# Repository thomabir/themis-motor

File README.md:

# Themis Telescope Mount

Hardware and software for a direct-drive brushless DC motor and encoder for a telescope mount

## Control Scheme

- PWM
  - 50 to 100 kHz
  - Input: desired PWM duty cycle
  - Output: PWM signals to gate drivers
- Inner Loop: Current Control (FOC)
  - Controls flux and torque currents.
  - Runs at 10–20 kHz.
  - Inputs: Torque target (from position control loop), Phase current measurements (from current sensor), rotor electrical angle (from encoder).
  - Outputs: PWM duty cycles via inverse Park/Clarke
- Outer Loop: Position Control
  - Controls angular position and/or velocity, which is commanded from the observatory
  - Runs at 100–500 Hz.
  - Inputs: Position setpoint, measured position from encoder
  - Output: Torque command

## Motor Specifications

- Type: BLDC, direct drive (salvaged from a hoverboard)
- Quantity: 2 motors
- Electrical: 3 Phases, 30 Poles, 27 Slots, 36 V, 13 A RMS peak, 7A RMS continuous, 0.45 Ω, Y
- Mechanical: ≈ 10 Nm continuous, ≈ 1.43 Nm/A, ≈ 16 rpm/V, 350 W (estimates, not necessarily accurate)

## Encoder

DIY inductosyn, 0.05 arcseconds resolution, 1000 Hz sampling rate, custom SPI-like interface with absolute position, latency 1 ms.

## System Requirements

- Telescope Alt/Az axis control
- Tracking speed: 1 rev / 24 hr
- Slewing speed: 1 rev / 10 s
- Tracking error: < 1 arcsecond RMS
- Power: Mains
- System inertia: Low (balanced 8" SCT)

Thermal: motor will be at low currents most of the time, so convection will probably be fine, with short peaks when slewing. (Motors are from a hoverboard, which was also only passively cooled)

Mechanical: Very low backlash; bearing friction (esp. static) likely to influence control scheme.

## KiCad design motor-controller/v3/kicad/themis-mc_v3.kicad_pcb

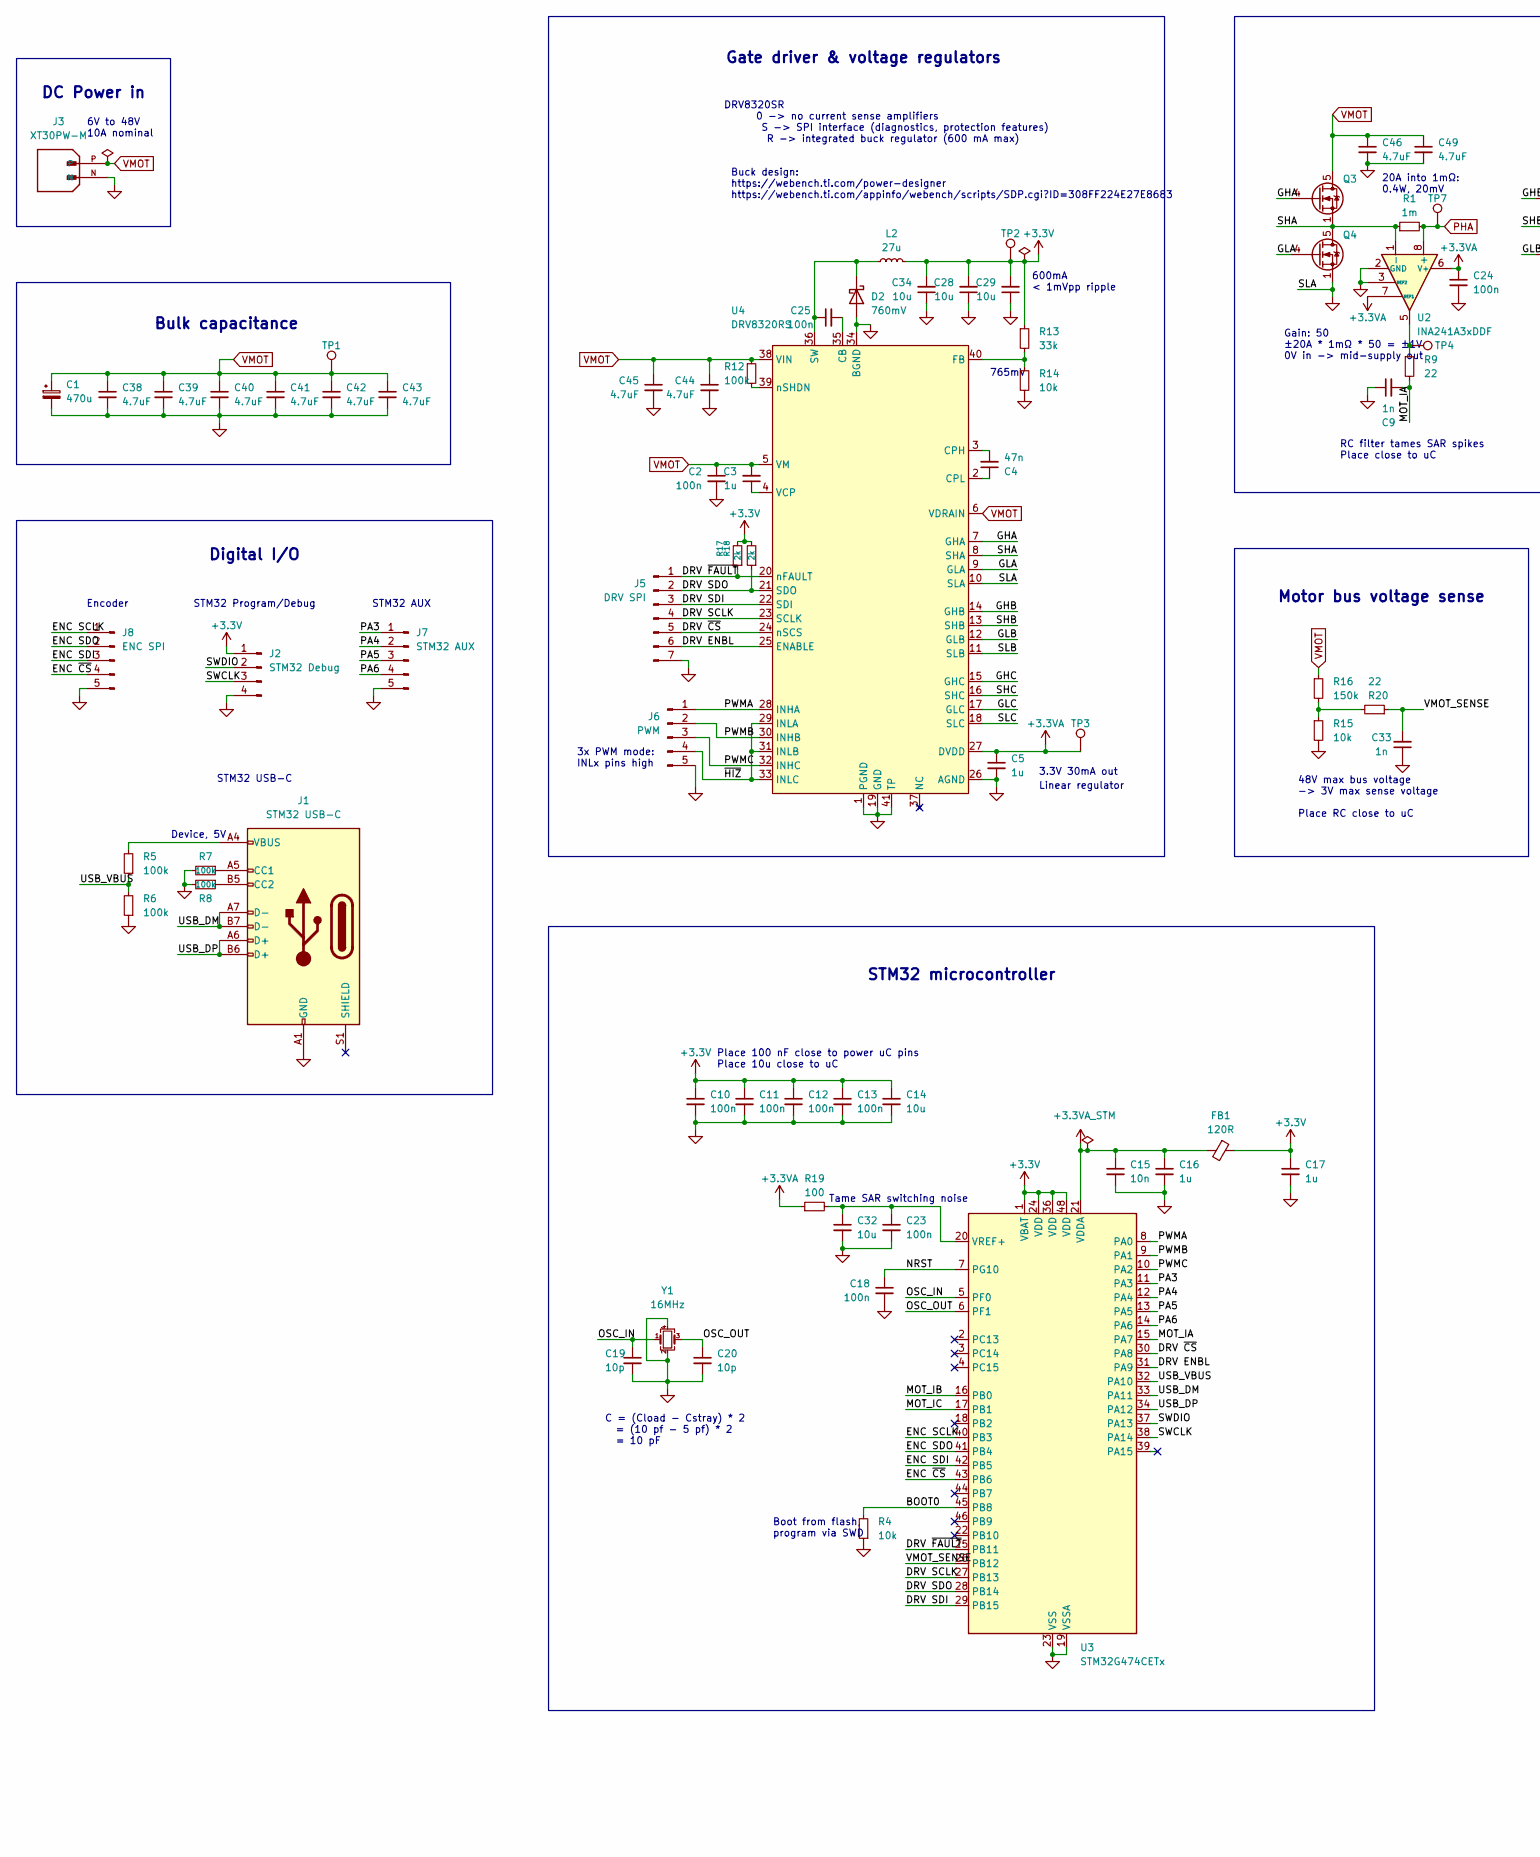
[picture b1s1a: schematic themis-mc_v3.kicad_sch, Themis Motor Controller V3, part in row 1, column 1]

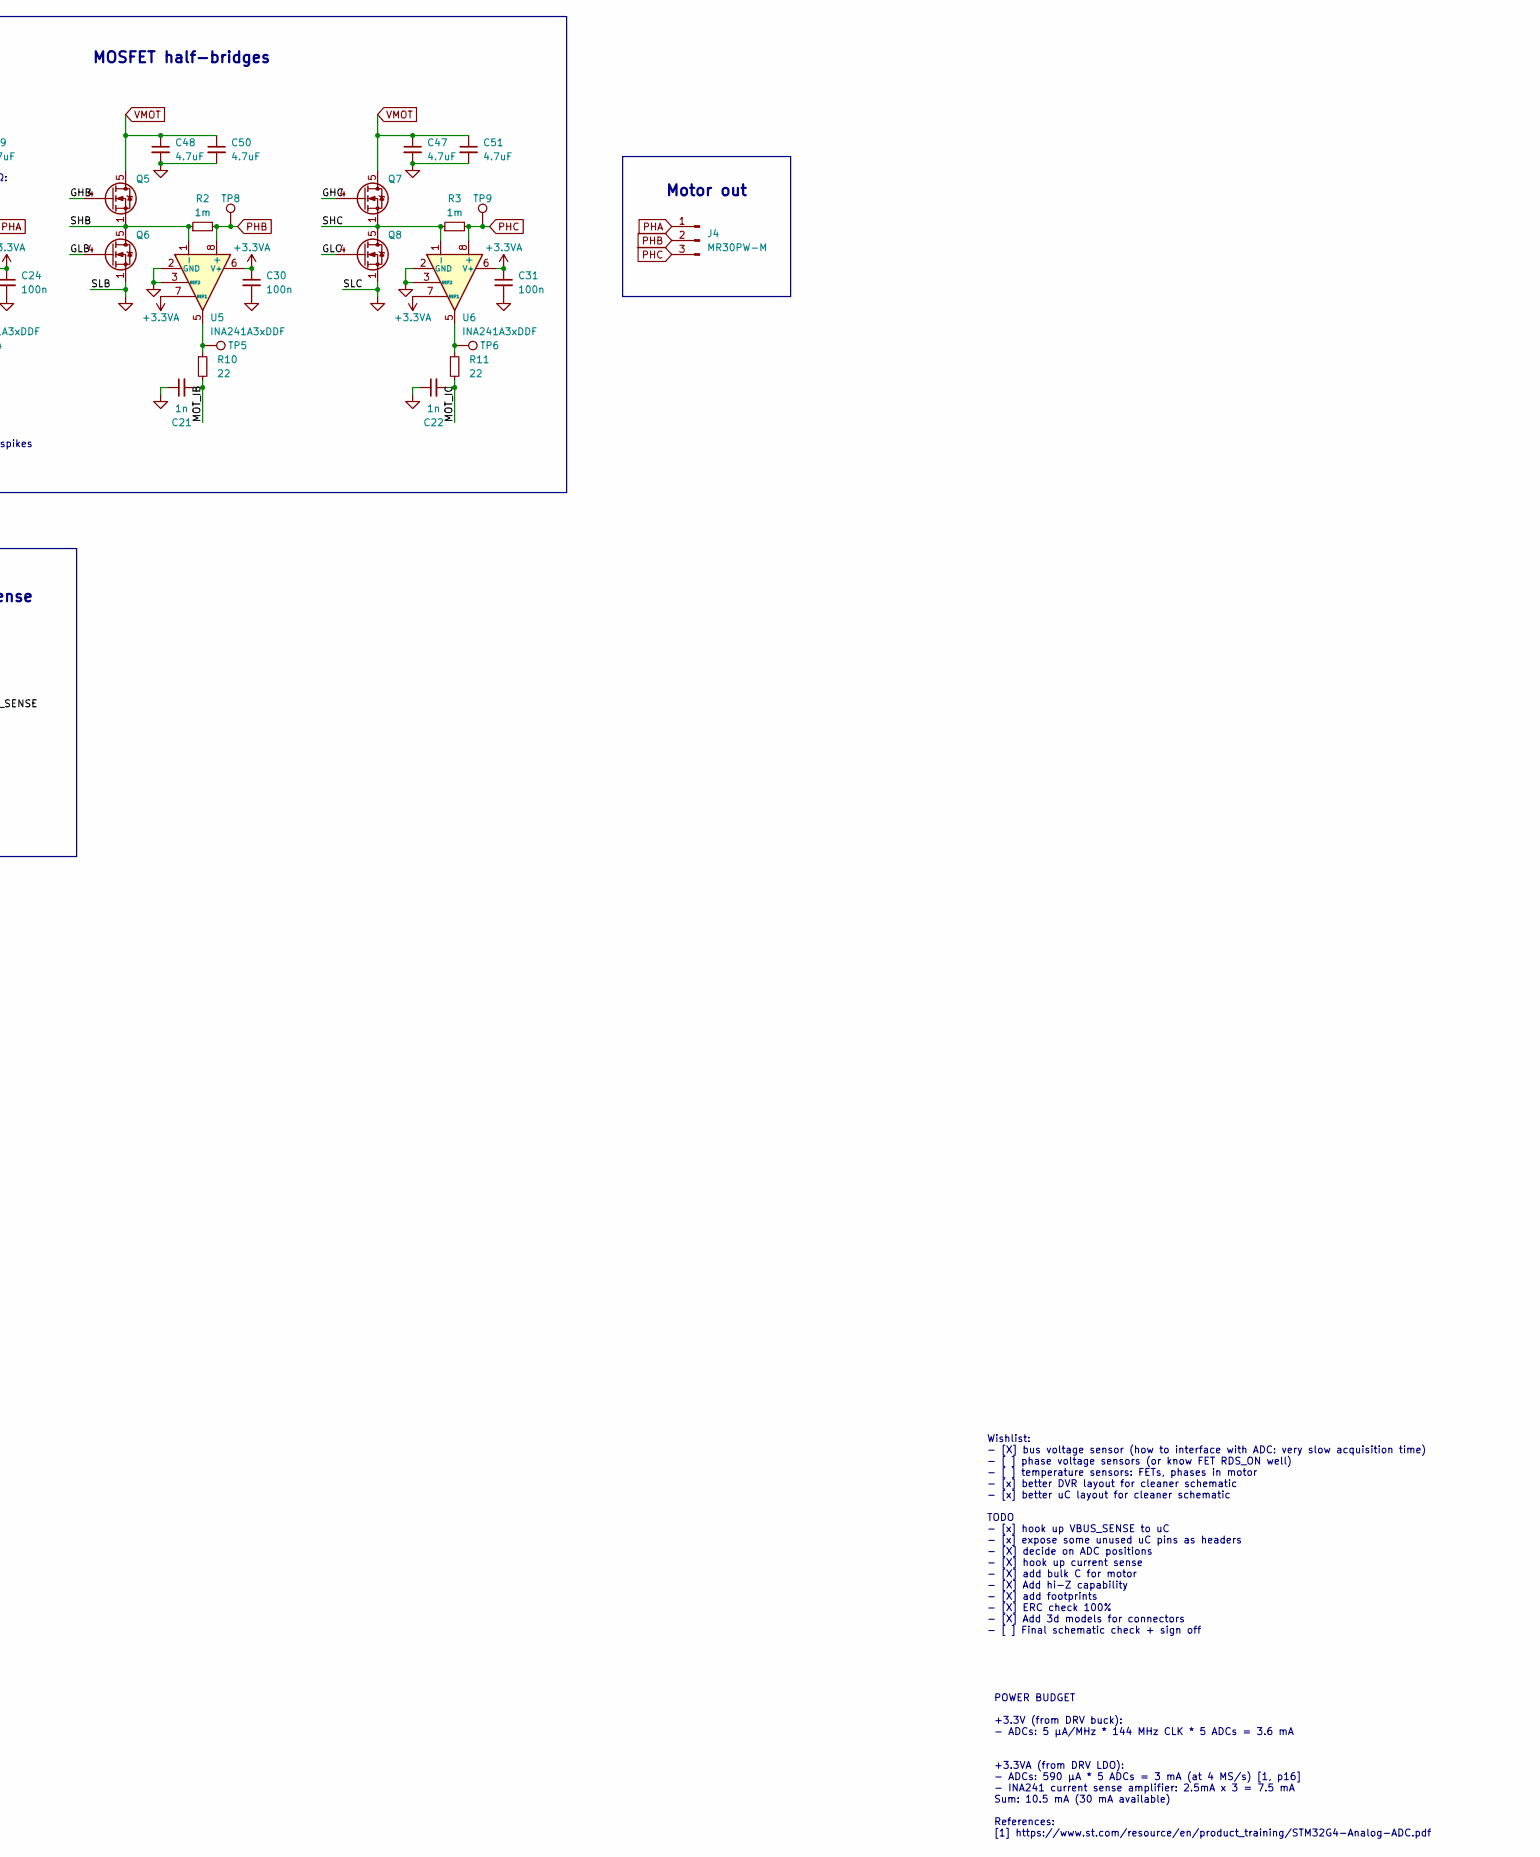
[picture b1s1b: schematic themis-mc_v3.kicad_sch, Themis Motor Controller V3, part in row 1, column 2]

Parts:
C1: 470u; CP_Radial_D16.0mm_P7.50mm; MPN 100ZLH470MEFC16X31.5
C2, C25: 100n; C_0805_2012Metric; MPN CL21B104KCFWPNE
C3: 1u
C4: 47n; C_0805_2012Metric; MPN CL21B473KCFNNNE
C5, C16, C17: 1u; C_0805_2012Metric
C9, C21, C22, C33: 1n; C_0805_2012Metric
C10, C11, C12, C13, C18, C23, C24, C30, C31: 100n; C_0805_2012Metric
C14, C32: 10u; C_0805_2012Metric
C15: 10n; C_0805_2012Metric
C19, C20: 10p; C_0805_2012Metric
C28, C29, C34: 10u; C_0805_2012Metric; MPN C2012X5R1V156M125AC
C38, C39, C40, C41, C42, C43, C44, C45, C46, C47, C48, C49, C50, C51: 4.7uF; C_1206_3216Metric; MPN GRJ31CC72A475KE01K
D2: 760mV; Nexperia_CFP3_SOD-123W; MPN MBR1H100SFT3G
FB1: 120R; L_0805_2012Metric
J1: STM32 USB-C; USB_C_Receptacle_GCT_USB4105-xx-A_16P_TopMnt_Horizontal
J2: STM32 Debug; PinHeader_1x04_P2.54mm_Vertical
J3: XT30PW-M; AMASS_XT30PW-M_1x02_P2.50mm_Horizontal; MPN XT30PW-M
J4: MR30PW-M; AMASS_MR30PW-M_1x03_P3.50mm_Horizontal
J5: DRV SPI; PinHeader_1x07_P2.54mm_Vertical
J6: PWM; PinHeader_1x05_P2.54mm_Vertical
J7: STM32 AUX; PinHeader_1x05_P2.54mm_Vertical
J8: ENC SPI; PinHeader_1x05_P2.54mm_Vertical
L2: 27u; L_Bourns_SDR0604; MPN SDR0604-270YL
Q3, Q4, Q5, Q6, Q7, Q8: LFPAK56; MPN PSMN5R2-60YL
R1, R2, R3: 1m; R_2512_6332Metric; MPN CSNL2512FT1L00
R4, R14, R15: 10k; L_0805_2012Metric
R5, R6, R7, R8, R12: 100k; L_0805_2012Metric
R9, R10, R11, R20: 22; L_0805_2012Metric
R13: 33k; L_0805_2012Metric
R16: 150k; L_0805_2012Metric
R17, R18: 2k; L_0805_2012Metric
R19: 100; L_0805_2012Metric
TP1, TP2, TP3, TP4, TP5, TP6, TP7, TP8, TP9: TestPoint_Keystone_5010-5014_Multipurpose; MPN 5010-5014
U2, U5, U6: INA241A3xDDF; SOT-23-8; MPN INA241A3IDDFR
U3: STM32G474CETx; LQFP-48_7x7mm_P0.5mm
U4: DRV8320RS; VQFN-40-1EP_5x5mm_P0.4mm_EP3.5x3.5mm; MPN DRV8320RS
Y1: 16MHz; Crystal_SMD_3225-4Pin_3.2x2.5mm; MPN CS00527-16M

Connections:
+3.3V: C10.1, C11.1, C12.1, C13.1, C14.1, C17.1, C28.2, C29.2, C34.2, FB1.1, J2.1, L2.1, R13.1, R17.2, R18.2, TP2.1, U3.1 (VBAT), U3.24 (VDD), U3.36 (VDD), U3.48 (VDD)
+3.3VA: C5.1, C24.1, C30.1, C31.1, R19.1, TP3.1, U2.6 (V+), U2.7 (REF1), U4.27 (DVDD), U5.6 (V+), U5.7 (REF1), U6.6 (V+), U6.7 (REF1)
+3.3VA_STM: C15.1, C16.1, FB1.2, U3.21 (VDDA)
/BOOT0: R4.2, U3.45 (PB8)
/DRV ENBL: J5.6, U3.31 (PA9), U4.25 (ENABLE)
/DRV SCLK: J5.4, U3.27 (PB13), U4.23 (SCLK)
/DRV SDI: J5.3, U3.29 (PB15), U4.22 (SDI)
/DRV SDO: J5.2, R18.1, U3.28 (PB14), U4.21 (SDO)
/DRV ~CS: J5.5, U3.30 (PA8), U4.24 (nSCS)
/DRV ~FAULT: J5.1, R17.1, U3.25 (PB11), U4.20 (nFAULT)
/ENC SCLK: J8.1, U3.40 (PB3)
/ENC SDI: J8.3, U3.42 (PB5)
/ENC SDO: J8.2, U3.41 (PB4)
/ENC ~CS: J8.4, U3.43 (PB6)
/GHA: Q3.4 (G), U4.7 (GHA)
/GHB: Q5.4 (G), U4.14 (GHB)
/GHC: Q7.4 (G), U4.15 (GHC)
/GLA: Q4.4 (G), U4.9 (GLA)
/GLB: Q6.4 (G), U4.12 (GLB)
/GLC: Q8.4 (G), U4.17 (GLC)
/MOT_IA: C9.2, R9.2, U3.15 (PA7)
/MOT_IB: C21.2, R10.2, U3.16 (PB0)
/MOT_IC: C22.2, R11.2, U3.17 (PB1)
/NRST: C18.1, U3.7 (PG10)
/OSC_IN: C19.1, U3.5 (PF0), Y1.1
/OSC_OUT: C20.1, U3.6 (PF1), Y1.3
/PA3: J7.1, U3.11 (PA3)
/PA4: J7.2, U3.12 (PA4)
/PA5: J7.3, U3.13 (PA5)
/PA6: J7.4, U3.14 (PA6)
/PWMA: J6.1, U3.8 (PA0), U4.28 (INHA)
/PWMB: J6.2, U3.9 (PA1), U4.30 (INHB)
/PWMC: J6.3, U3.10 (PA2), U4.32 (INHC)
/SHA: Q3.1 (S), Q3.2 (S), Q3.3 (S), Q4.5 (D), R1.1, U2.1 (-), U4.8 (SHA)
/SHB: Q5.1 (S), Q5.2 (S), Q5.3 (S), Q6.5 (D), R2.1, U4.13 (SHB), U5.1 (-)
/SHC: Q7.1 (S), Q7.2 (S), Q7.3 (S), Q8.5 (D), R3.1, U4.16 (SHC), U6.1 (-)
/SWCLK: J2.3, U3.38 (PA14)
/SWDIO: J2.2, U3.37 (PA13)
/USB_DM: J1.A7 (D-), J1.B7 (D-), U3.33 (PA11)
/USB_DP: J1.A6 (D+), J1.B6 (D+), U3.34 (PA12)
/USB_VBUS: R5.1, R6.2, U3.32 (PA10)
/VMOT_SENSE: C33.2, R20.1, U3.26 (PB12)
/~HIZ: J6.4, U4.29 (INLA), U4.31 (INLB), U4.33 (INLC)
GND: C1.2, C2.2, C5.2, C9.1, C10.2, C11.2, C12.2, C13.2, C14.2, C15.2, C16.2, C17.2, C18.2, C19.2, C20.2, C21.1, C22.1, C23.2, C24.2, C28.1, C29.1, C30.2, C31.2, C32.2, C33.1, C34.1, C38.2, C39.2, C40.2, C41.2, C42.2, C43.2, C44.2, C45.2, C46.2, C47.2, C48.2, C49.2, C50.2, C51.2, D2.2 (A), J1.A1 (GND), J1.A12 (GND), J1.B1 (GND), J1.B12 (GND), J2.4, J3.N, J5.7, J6.5, J7.5, J8.5, Q4.1 (S), Q4.2 (S), Q4.3 (S), Q6.1 (S), Q6.2 (S), Q6.3 (S), Q8.1 (S), Q8.2 (S), Q8.3 (S), R4.1, R6.1, R7.2, R8.2, R14.2, R15.2, U2.2 (GND), U2.3 (REF2), U2.4 (GND), U3.19 (VSSA), U3.23 (VSS), U3.35 (VSS), U3.47 (VSS), U4.1 (PGND), U4.10 (SLA), U4.11 (SLB), U4.18 (SLC), U4.19 (GND), U4.26 (AGND), U4.34 (BGND), U4.41 (TP), U5.2 (GND), U5.3 (REF2), U5.4 (GND), U6.2 (GND), U6.3 (REF2), U6.4 (GND), Y1.2, Y1.4
unnamed: C25.1, D2.1 (K), L2.2, U4.36 (SW)
unnamed: J1.A5 (CC1), R7.1
unnamed: J1.B5 (CC2), R8.1
unnamed: J1.A4 (VBUS), J1.A9 (VBUS), J1.B4 (VBUS), J1.B9 (VBUS), R5.2
unnamed: R9.1, TP4.1, U2.5
unnamed: R10.1, TP5.1, U5.5
unnamed: R11.1, TP6.1, U6.5
unnamed: R15.1, R16.2, R20.2
unnamed: C23.1, C32.1, R19.2, U3.20 (VREF+)
unnamed: C25.2, U4.35 (CB)
unnamed: C4.2, U4.3 (CPH)
unnamed: C4.1, U4.2 (CPL)
unnamed: R13.2, R14.1, U4.40 (FB)
unnamed: C3.1, U4.4 (VCP)
unnamed: R12.2, U4.39 (nSHDN)
PHA: J4.1, R1.2, TP7.1, U2.8 (+)
PHB: J4.2, R2.2, TP8.1, U5.8 (+)
PHC: J4.3, R3.2, TP9.1, U6.8 (+)
VMOT: C1.1, C2.1, C3.2, C38.1, C39.1, C40.1, C41.1, C42.1, C43.1, C44.1, C45.1, C46.1, C47.1, C48.1, C49.1, C50.1, C51.1, J3.P, Q3.5 (D), Q5.5 (D), Q7.5 (D), R12.1, R16.1, TP1.1, U4.5 (VM), U4.6 (VDRAIN), U4.38 (VIN)

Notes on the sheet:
6V to 48V 10A nominal
STM32 USB-C
600mA < 1mVpp ripple
STM32 AUX
20A into 1mΩ: 0.4W, 20mV
Gain: 50 ±20A * 1mΩ * 50 = ±1V 0V in -> mid-supply out
MOSFET half-bridges
Linear regulator
48V max bus voltage -> 3V max sense voltage
Bulk capacitance
Motor out
Motor bus voltage sense
765mV
Place 100 nF close to power uC pins Place 10u close to uC
Gate driver & voltage regulators
3.3V 30mA out
Buck design: https://webench.ti.com/power-designer https://webench.ti.com/appinfo/webench/scripts/SDP.cgi?ID=308FF224E27E8683
Wishlist: - [X] bus voltage sensor (how to interface with ADC: very slow acquisition time) - [ ] phase voltage sensors (or know FET RDS_ON well) - [ ] temperature sensors: FETs, phases in motor - [x] better DVR layout for cleaner schematic - [x] better uC layout for cleaner schematic TODO - [x] hoo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
C = (Cload - Cstray) * 2 = (10 pf - 5 pf) * 2 = 10 pF
3x PWM mode: INLx pins high
Encoder
Digital I/O
Tame SAR switching noise
Device, 5V
DRV8320SR 0 -> no current sense amplifiers S -> SPI interface (diagnostics, protection features) R -> integrated buck regulator (600 mA max)
POWER BUDGET +3.3V (from DRV buck): - ADCs: 5 µA/MHz * 144 MHz CLK * 5 ADCs = 3.6 mA +3.3VA (from DRV LDO): - ADCs: 590 μA * 5 ADCs = 3 mA (at 4 MS/s) [1, p16] - INA241 current sense amplifier: 2.5mA x 3 = 7.5 mA Sum: 10.5 mA (30 mA available) References: [1] https://www.st.com/resource/en/product_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
Place RC close to uC
STM32 Program/Debug
Boot from flash, program via SWD
RC filter tames SAR spikes Place close to uC
DC Power in
STM32 microcontroller

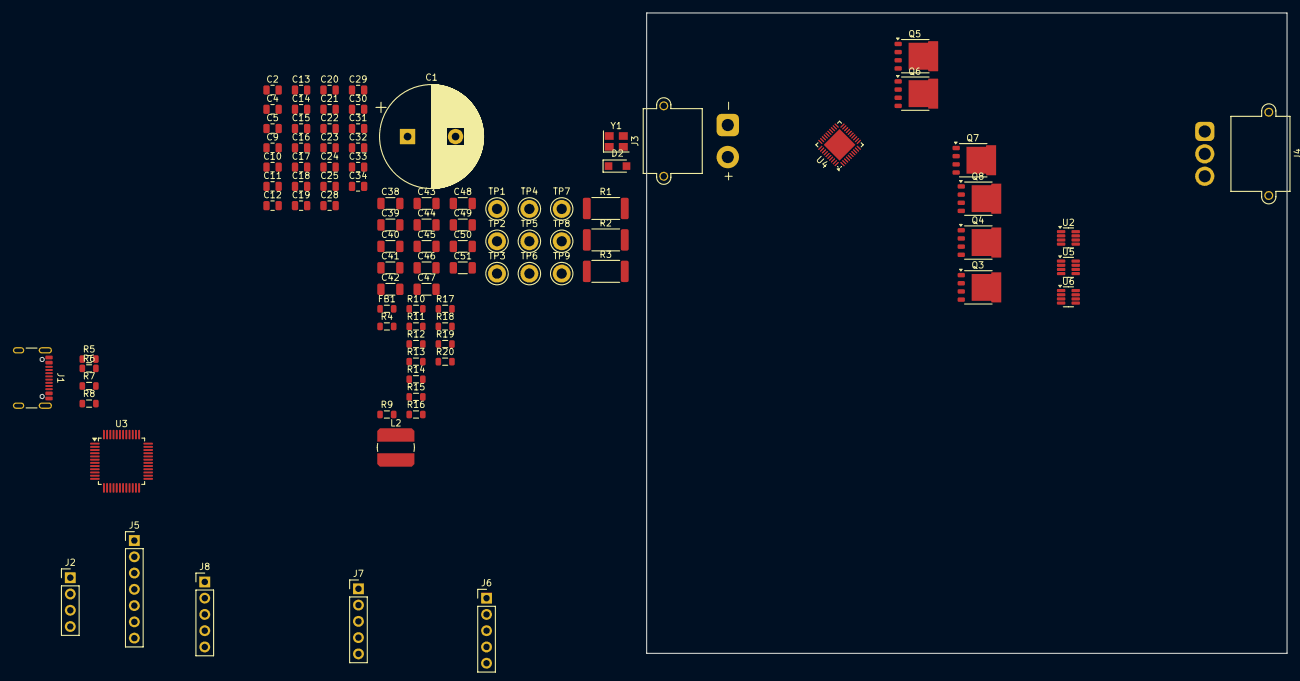
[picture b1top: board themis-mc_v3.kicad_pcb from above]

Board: 2 copper layers, 100.0 x 100.0 mm, 94 parts (0 on the bottom side), 62 nets.

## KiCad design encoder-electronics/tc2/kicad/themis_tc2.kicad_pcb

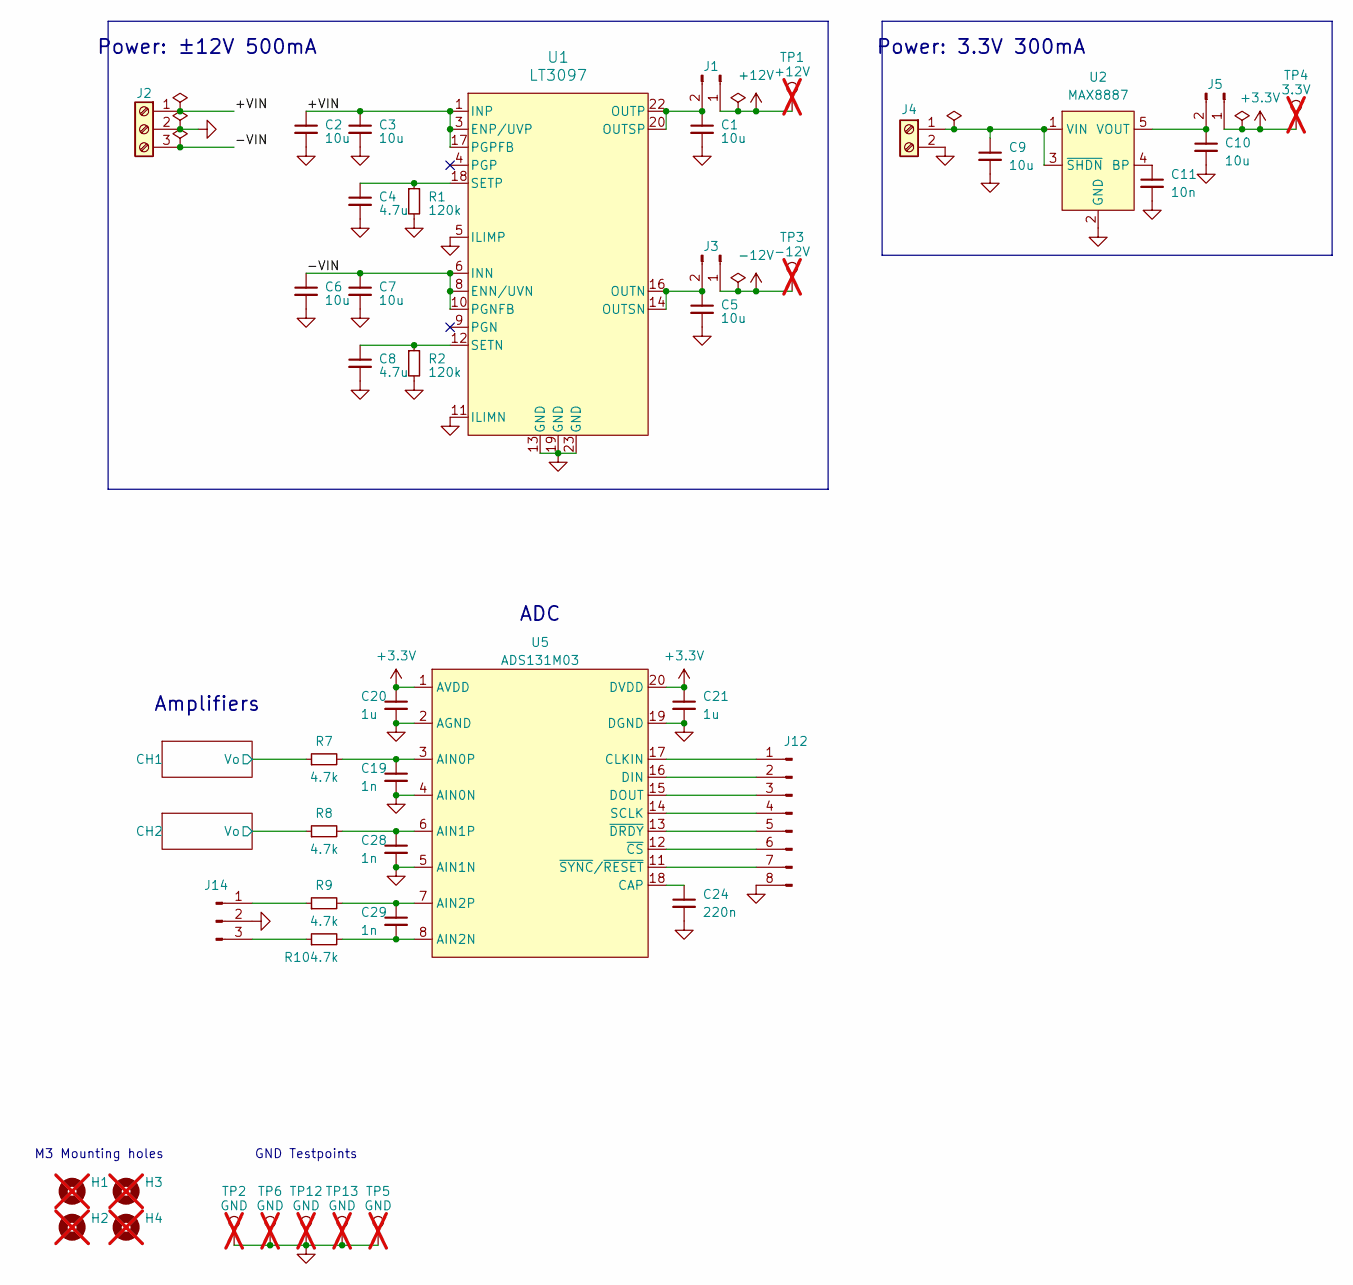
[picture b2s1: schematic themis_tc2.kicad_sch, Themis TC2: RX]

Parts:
C1, C2, C3, C5, C6, C7, C9, C10: 10u; C_0805_2012Metric; MPN GRM21BR61H106KE43L
C4, C8: 4.7u; C_0805_2012Metric; MPN GRM21BR61H475KE51L
C11: 10n; C_0805_2012Metric; MPN C0805C103K5RACTU
C19, C28, C29: 1n; C_0805_2012Metric; MPN C0805C102J5GACTU
C20, C21: 1u; C_0805_2012Metric; MPN CL21B105KBFNNNE
C24: 220n; C_0805_2012Metric; MPN CL21B224KBFNNNE
H1, H2, H3, H4: MountingHole; MountingHole_3.2mm_M3_DIN965; not fitted
J1, J3, J5: Conn_01x02_Pin; PinHeader_1x02_P2.54mm_Vertical; MPN 61300211121
J2: Screw_Terminal_01x03; TerminalBlock_TE_282834-3_1x03_P2.54mm_Horizontal; MPN 282834-3
J4: Screw_Terminal_01x02; TerminalBlock_TE_282834-2_1x02_P2.54mm_Horizontal; MPN 282834-2
J12: Conn_01x08_Pin; PinHeader_1x08_P2.54mm_Vertical; MPN 61300811121
J14: Conn_01x03_Pin; PinHeader_1x03_P2.54mm_Vertical; MPN 61300311121
R1, R2: 120k; R_0805_2012Metric; MPN RC0805FR-07120KL
R7, R8, R9, R10: 4.7k; R_0805_2012Metric; MPN RC0805FR-074K7L
TP1: +12V; TestPoint_Keystone_5010-5014_Multipurpose; not fitted
TP2, TP5, TP6, TP12, TP13: GND; TestPoint_Keystone_5010-5014_Multipurpose; not fitted
TP3: -12V; TestPoint_Keystone_5010-5014_Multipurpose; not fitted
TP4: 3.3V; TestPoint_Keystone_5010-5014_Multipurpose; not fitted
U1: LT3097; 05-08-7071_ADI; MPN LT3097ADJC#PBF
U2: MAX8887; SOT-23-5; MPN MAX8887EZK33+T
U5: ADS131M03; TSSOP-20_L6.5-W4.4-P0.65-LS6.4-BL; MPN ADS131M03QPWRQ1; LCSC Part C6123452

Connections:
+3.3V: C20.1, C21.1, J5.1, TP4.1, U5.1 (AVDD), U5.20 (DVDD)
+12V: J1.1, TP1.1; also elsewhere on the board
-12V: J3.1, TP3.1; also elsewhere on the board
/CH1/Vo: R7.1; also elsewhere on the board
/CH2/Vo: R8.1; also elsewhere on the board
GND: C1.2, C2.2, C3.2, C4.2, C5.2, C6.2, C7.2, C8.2, C9.2, C10.2, C11.2, C19.2, C20.2, C21.2, C24.2, C28.2, J2.2, J4.2, J12.8, J14.2, R1.2, R2.2, TP2.1, TP5.1, TP6.1, TP12.1, TP13.1, U1.5 (ILIMP), U1.11 (ILIMN), U1.13 (GND), U1.19 (GND), U1.23 (GND), U2.2 (GND), U5.2 (AGND), U5.4 (AIN0N), U5.5 (AIN1N), U5.19 (DGND); also elsewhere on the board
INN: C6.1, C7.1, J2.3, U1.6 (INN), U1.7 (INN), U1.8 (ENN/UVN), U1.10 (PGNFB), U1.24 (INN)
INP: C2.1, C3.1, J2.1, U1.1 (INP), U1.2 (INP), U1.3 (ENP/UVP), U1.17 (PGPFB)
unnamed: C1.1, J1.2, U1.20 (OUTSP), U1.21 (OUTP), U1.22 (OUTP)
unnamed: C5.1, J3.2, U1.14 (OUTSN), U1.15 (OUTN), U1.16 (OUTN)
unnamed: C9.1, J4.1, U2.1 (VIN), U2.3 (~SHDN)
unnamed: C10.1, J5.2, U2.5 (VOUT)
unnamed: J12.1, U5.17 (CLKIN)
unnamed: J12.2, U5.16 (DIN)
unnamed: J12.3, U5.15 (DOUT)
unnamed: J12.4, U5.14 (SCLK)
unnamed: J12.5, U5.13 (~DRDY)
unnamed: J12.6, U5.12 (~CS)
unnamed: J12.7, U5.11 (~SYNC/~RESET)
unnamed: J14.1, R9.1
unnamed: J14.3, R10.1
unnamed: C8.1, R2.1, U1.12 (SETN)
unnamed: C4.1, R1.1, U1.18 (SETP)
unnamed: C11.1, U2.4 (BP)
unnamed: C19.1, R7.2, U5.3 (AIN0P)
unnamed: C28.1, R8.2, U5.6 (AIN1P)
unnamed: C29.2, R10.2, U5.8 (AIN2N)
unnamed: C29.1, R9.2, U5.7 (AIN2P)
unnamed: C24.1, U5.18 (CAP)

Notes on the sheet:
ADC
M3 Mounting holes
GND Testpoints
Power: 3.3V 300mA
Amplifiers
Power: ±12V 500mA

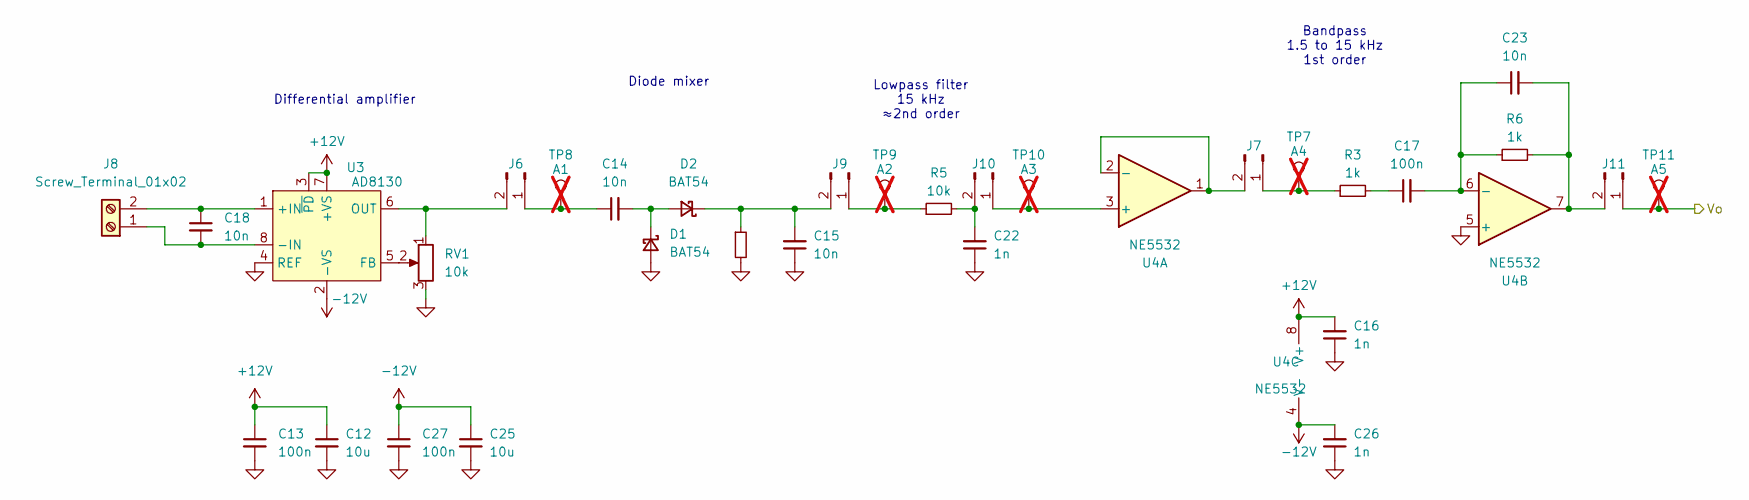
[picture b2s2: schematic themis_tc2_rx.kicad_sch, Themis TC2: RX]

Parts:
C12, C25: 10u; C_0805_2012Metric; MPN GRM21BR61H106KE43L
C13, C17, C27: 100n; C_0805_2012Metric; MPN C0805C104K5RACTU
C14, C15, C18, C23: 10n; C_0805_2012Metric; MPN C0805C103K5RACTU
C16, C22, C26: 1n; C_0805_2012Metric; MPN C0805C102J5GACTU
D1, D2: BAT54; D_SOD-323; MPN BAT54HT1G
J6, J7, J9, J10, J11: Conn_01x02_Pin; PinHeader_1x02_P2.54mm_Vertical; MPN 61300211121
J8: Screw_Terminal_01x02; TerminalBlock_TE_282834-2_1x02_P2.54mm_Horizontal; MPN 282834-2
R3, R4, R6: 1k; R_0805_2012Metric; MPN RC0805FR-071KL
R5: 10k; R_0805_2012Metric; MPN RC0805FR-0710KL
RV1: 10k; Potentiometer_Bourns_3296W_Vertical; MPN 3296W-1-103LF
TP7: A4; TestPoint_Keystone_5010-5014_Multipurpose; not fitted
TP8: A1; TestPoint_Keystone_5010-5014_Multipurpose; not fitted
TP9: A2; TestPoint_Keystone_5010-5014_Multipurpose; not fitted
TP10: A3; TestPoint_Keystone_5010-5014_Multipurpose; not fitted
TP11: A5; TestPoint_Keystone_5010-5014_Multipurpose; not fitted
U3: AD8130; SOIC-8_L4.9-W3.9-P1.27-LS6.0-BL; MPN AD8130ARMZ-REEL; LCSC Part C126440
U4: NE5532; SOIC-8_3.9x4.9mm_P1.27mm; MPN NE5532DR

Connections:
+12V: C12.1, C13.1, C16.2, U3.3 (~PD), U3.7 (+VS), U4.8 (V+); also elsewhere on the board
-12V: C25.1, C26.2, C27.1, U3.2 (-VS), U4.4 (V-); also elsewhere on the board
/CH1/Vo: J11.1, TP11.1; also elsewhere on the board
GND: C12.2, C13.2, C15.1, C16.1, C22.1, C25.2, C26.1, C27.2, D1.2 (A), R4.2, RV1.3, U3.4 (REF), U4.5 (+); also elsewhere on the board
unnamed: C17.1, R3.2
unnamed: C14.2, D1.1 (K), D2.2 (A)
unnamed: C15.2, D2.1 (K), J9.2, R4.1
unnamed: C14.1, J6.1, TP8.1
unnamed: J6.2, RV1.1, U3.6 (OUT)
unnamed: J7.1, R3.1, TP7.1
unnamed: J7.2, U4.1, U4.2 (-)
unnamed: C18.2, J8.1, U3.8 (-IN)
unnamed: C18.1, J8.2, U3.1 (+IN)
unnamed: J9.1, R5.1, TP9.1
unnamed: J10.1, TP10.1, U4.3 (+)
unnamed: C22.2, J10.2, R5.2
unnamed: C23.2, J11.2, R6.2, U4.7
unnamed: RV1.2, U3.5 (FB)
unnamed: C17.2, C23.1, R6.1, U4.6 (-)

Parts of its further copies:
C30, C39: 10u; C_0805_2012Metric; MPN GRM21BR61H106KE43L
C31, C34, C40: 100n; C_0805_2012Metric; MPN C0805C104K5RACTU
C32, C33, C36, C38: 10n; C_0805_2012Metric; MPN C0805C103K5RACTU
C35, C37, C41: 1n; C_0805_2012Metric; MPN C0805C102J5GACTU
D3, D4: BAT54; D_SOD-323; MPN BAT54HT1G
J13, J15, J17, J18, J19: Conn_01x02_Pin; PinHeader_1x02_P2.54mm_Vertical; MPN 61300211121
J16: Screw_Terminal_01x02; TerminalBlock_TE_282834-2_1x02_P2.54mm_Horizontal; MPN 282834-2
R11, R12, R14: 1k; R_0805_2012Metric; MPN RC0805FR-071KL
R13: 10k; R_0805_2012Metric; MPN RC0805FR-0710KL
RV2: 10k; Potentiometer_Bourns_3296W_Vertical; MPN 3296W-1-103LF
TP14: A4; TestPoint_Keystone_5010-5014_Multipurpose; not fitted
TP15: A1; TestPoint_Keystone_5010-5014_Multipurpose; not fitted
TP16: A2; TestPoint_Keystone_5010-5014_Multipurpose; not fitted
TP17: A3; TestPoint_Keystone_5010-5014_Multipurpose; not fitted
TP18: A5; TestPoint_Keystone_5010-5014_Multipurpose; not fitted
U6: AD8130; SOIC-8_L4.9-W3.9-P1.27-LS6.0-BL; MPN AD8130ARMZ-REEL; LCSC Part C126440
U7: NE5532; SOIC-8_3.9x4.9mm_P1.27mm; MPN NE5532DR

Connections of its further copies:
+12V: C30.1, C31.1, C35.2, U6.3 (~PD), U6.7 (+VS), U7.8 (V+); also elsewhere on the board
-12V: C39.1, C40.1, C41.2, U6.2 (-VS), U7.4 (V-); also elsewhere on the board
/CH2/Vo: J19.1, TP18.1; also elsewhere on the board
GND: C30.2, C31.2, C33.1, C35.1, C37.1, C39.2, C40.2, C41.1, D3.2 (A), R12.2, RV2.3, U6.4 (REF), U7.5 (+); also elsewhere on the board
unnamed: C34.1, R11.2
unnamed: C32.2, D3.1 (K), D4.2 (A)
unnamed: C33.2, D4.1 (K), J17.2, R12.1
unnamed: C32.1, J13.1, TP15.1
unnamed: J13.2, RV2.1, U6.6 (OUT)
unnamed: J15.1, R11.1, TP14.1
unnamed: J15.2, U7.1, U7.2 (-)
unnamed: C36.2, J16.1, U6.8 (-IN)
unnamed: C36.1, J16.2, U6.1 (+IN)
unnamed: J17.1, R13.1, TP16.1
unnamed: J18.1, TP17.1, U7.3 (+)
unnamed: C37.2, J18.2, R13.2
unnamed: C38.2, J19.2, R14.2, U7.7
unnamed: RV2.2, U6.5 (FB)
unnamed: C34.2, C38.1, R14.1, U7.6 (-)

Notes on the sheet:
Differential amplifier
Diode mixer
Bandpass 1.5 to 15 kHz 1st order
Lowpass filter 15 kHz ≈2nd order

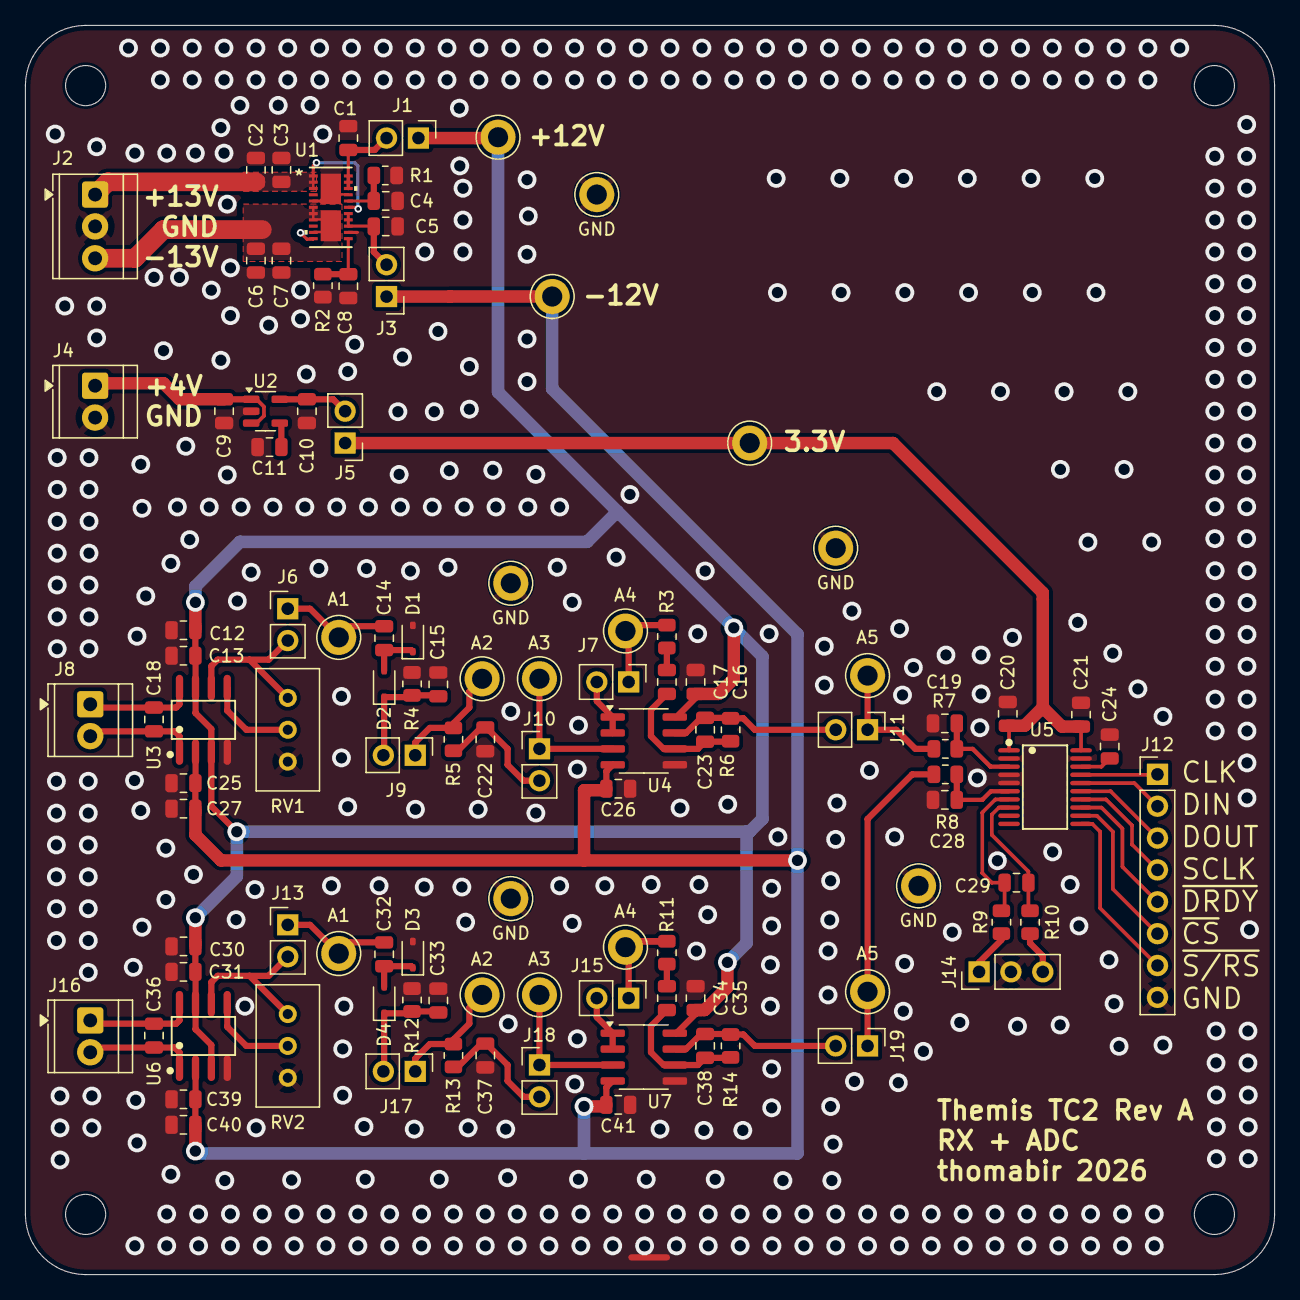
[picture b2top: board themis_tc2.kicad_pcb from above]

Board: 4 copper layers, 99.6 x 99.6 mm, 109 parts (0 on the bottom side), 59 nets.
